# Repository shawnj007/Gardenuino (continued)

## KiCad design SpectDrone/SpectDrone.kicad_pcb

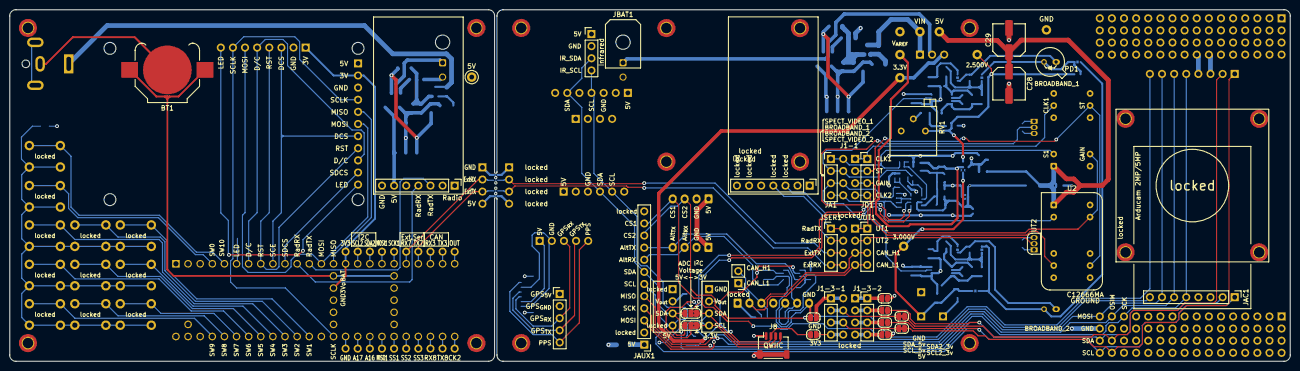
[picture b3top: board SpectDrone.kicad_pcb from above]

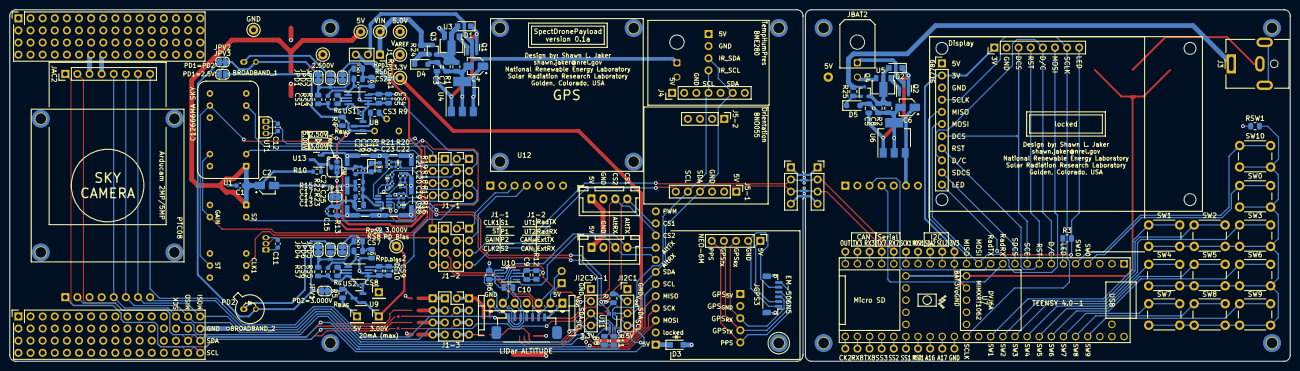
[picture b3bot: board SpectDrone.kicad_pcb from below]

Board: 4 copper layers, 268.4 x 73.7 mm, 233 parts (157 on the bottom side), 135 nets.

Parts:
BT1: Battery_Cell; BatteryHolder_Keystone_3000_1x12mm
C1, C11, C12, C14, C27: 0.1uF; C_0603_1608Metric
C2, C4, C6: 10uF; CP_Elec_3x5.4
C3, C5, C7, C8, C9, C10: 0.1uF; C_0805_2012Metric
C13: 10uF; C_0805_2012Metric
C15: 2.5pF; C_0402_1005Metric
C16: X; CP_EIA-2012-15_AVX-P
C17: X; C_0603_1608Metric
C18, C19, C20, C21, C22, C23, C24, C25: X; C_0402_1005Metric
C26: 1pF; C_0402_1005Metric
C28, C29: C_Polarized; C_Elec_6.3x7.7
CS1, CS6: 11.1pF; C_0603_1608Metric
CS2, CS3, CS7, CS8: 1.11pF; C_0402_1005Metric
CS4, CS9: 10uF; C_0805_2012Metric
CS5, CS10: 0.1uF; C_0805_2012Metric
D1, D2: D; Nexperia_CFP3_SOD-123W
D3: Ge; Nexperia_CFP3_SOD-123W
D4, D5: HPZR-C6V7X; D_SOD-123F
H1, H2, H3, H4, H5, H6, H7, H8, H9, H10, H11, H12, H13, H14, H15, H16: MountingHole; MountingHole_2.2mm_M2_ISO14580_Pad_TopBottom
H17, H18, H19, H20: MountingHole; MountingHole_2.5mm
J1: Conn_01x03_Socket; PinSocket_1x03_P2.54mm_Vertical
J1-1: Conn_02x03_Counter_Clockwise; PinSocket_2x04_P2.54mm_Vertical_renumber
J1-3-1, J1-3-2: Conn_01x04_Male; PinHeader_1x04_P2.54mm_Vertical
J3: Barrel_Jack; BarrelJack_CUI_PJ-063AH_Horizontal
J3V0-1, J5V3-2: Conn_01x01_Male; PinHeader_1x01_P2.54mm_Vertical
J3V2: Conn_01x01_Female; SolderWire-0.1sqmm_1x01_D0.4mm_OD1mm
J4: BME280; PinHeader_1x07_P2.54mm_Vertical
J5: RFShield_OnePiece; Laird_Technologies_BMI-S-101_13.66x12.70mm
J5-1: BNO055-1; PinHeader_1x06_P2.54mm_Vertical
J5-2: BNO055-2; PinHeader_1x04_P2.54mm_Vertical
J6, J7: Conn_02x16_Counter_Clockwise; PinSocket_4x16_P2.54mm_Vertical
J8: QWICK; JST_SH_SM04B-SRSS-TB_1x04-1MP_P1.00mm_Horizontal
JA1: Conn_01x04_Male; PinHeader_1x04_P2.54mm_Vertical
JA10, JA11, JA12, JA13, JA16, JA17: Conn_01x01_Female; SolderWire-0.1sqmm_1x01_D0.4mm_OD1mm
JAC1, JAC2: Conn_01x08_Female; ArduCam2MP
JALT1: ALTITUDE; JST_EH_S7B-EH_1x07_P2.50mm_Horizontal
JALT2: ALTITUDE; PicoBlade_1x07-1MP_P1.25mm_Horizontal
JAPC-1, JAPC-2: APC220; PinHeader_1x07_P2.54mm_Vertical
JAUX1: AUX; PinHeader_1x12_P2.54mm_Vertical
JBAT1, JBAT2: Conn_01x02_Female; Molex_Micro-Fit_3.0_43045-0200_2x01_P3.00mm_Horizontal
JCAM1, JCAM2: Camera; JST_XH_B4B-XH-A_1x04_P2.50mm_Vertical
JCK2: Conn_01x01_Female; SolderWire-0.1sqmm_1x01_D0.4mm_OD1mm
JD1: Conn_01x04_Male; PinHeader_1x04_P2.54mm_Vertical
JDIS1: Display; PinHeader_1x08_P2.54mm_Vertical
JDIS2: Display; PinHeader_1x11_P2.54mm_Vertical
JGND1: Conn_01x01_Female; SolderWire-0.1sqmm_1x01_D0.4mm_OD1mm
JGND1-2: Conn_01x01_Male; PinHeader_1x01_P2.54mm_Vertical
JGPS1, JGPS2: GPS; PinHeader_1x05_P2.54mm_Vertical
JGPS3: GPS; JST_SH_BM06B-SRSS-TB_1x06-1MP_P1.00mm_Vertical
JI2C1, JI2C3v-1: Conn_01x04_Male; PinHeader_1x04_P2.54mm_Vertical
JIF1: Payload; PinHeader_1x04_P2.54mm_Vertical
JIF2: Base; PinSocket_1x04_P2.54mm_Vertical
JIR1: Infrared; PinHeader_1x04_P2.54mm_Vertical
JMISO1: Conn_01x01_Female; SolderWire-0.1sqmm_1x01_D0.4mm_OD1mm
JOUT1: Conn_01x01_Female; SolderWire-0.1sqmm_1x01_D0.4mm_OD1mm
JP3, JP4, JP5, JP6, JP9, JP10: SolderJumper_2_Open; SolderJumper-2_P1.3mm_Open_RoundedPad1.0x1.5mm
JP7: SolderJumper_2_Bridged; SolderJumper-2_P1.3mm_Bridged_RoundedPad1.0x1.5mm
JP8: SolderJumper_2_Open; SolderJumper-2_P1.3mm_Bridged_RoundedPad1.0x1.5mm
JP11: SolderJumper_2_Bridged; SolderJumper-2_P1.3mm_Bridged2Bar_RoundedPad1.0x1.5mm
JP12, JP13, JP14, JP15: SolderJumper_2_Bridged; BreakableJumper
JP16: SolderJumper_3_Bridged12; SolderJumper-4_P1.3mm_Bridged2Bar12_RoundedPad
JP17, JP18: SolderJumper_3_Bridged12; SolderJumper-3_P1.3mm_Bridged2Bar12_RoundedPad1.0x1.5mm
JPD1, JPD3, JPD4, JPD6: SolderJumper_2_Bridged; SolderJumper-2_P1.3mm_Bridged_RoundedPad1.0x1.5mm
JPD2, JPD5: SolderJumper_2_Open; SolderJumper-2_P1.3mm_Open_RoundedPad1.0x1.5mm
JPV1, JPV2: SolderJumper_2_Bridged; SolderJumper-2_P1.3mm_Bridged_RoundedPad1.0x1.5mm
JPV3: SolderJumper_2_Open; SolderJumper-2_P1.3mm_Open_RoundedPad1.0x1.5mm
JRX3, JRX7, JRX8: Conn_01x01_Female; SolderWire-0.1sqmm_1x01_D0.4mm_OD1mm
JSER1: Conn_01x04_Male; PinHeader_1x04_P2.54mm_Vertical
JSS1, JSS2, JSS3: Conn_01x01_Female; SolderWire-0.1sqmm_1x01_D0.4mm_OD1mm
JTX3, JTX7, JTX8: Conn_01x01_Female; SolderWire-0.1sqmm_1x01_D0.4mm_OD1mm
JUT1: Conn_01x04_Male; PinHeader_1x04_P2.54mm_Vertical
PD1, PD2: S1336-18BK; S1336
Q1, Q2: FDN340P; SOT-23
Q3, Q4: NPN 50V 1A NPN_BEC; SOT-323_SC-70
R1, R2: 100K; R_0805_2012Metric
R3: 330; R_0805_2012Metric
R4: 250; R_0805_2012Metric
R5: 91; R_0805_2012Metric
R6, R7, R12: 200K; R_0805_2012Metric
R8, R11: 2K2; R_0805_2012Metric
R9: 470K; R_0805_2012Metric
R10: 20; R_0603_1608Metric
R13: 2K; R_0805_2012Metric
R14: 0; R_0603_1608Metric
R15: X; R_0603_1608Metric
R16, R18, R20, R22: 0; R_0402_1005Metric
R17, R19, R21, R23: X; R_0402_1005Metric
R24, R25: 10K; R_0805_2012Metric
RS2, RS5: R_{G}=X; R_0805_2012Metric
RS3, RS6, RS7, RS8: 330; R_0805_2012Metric
RSW1: 10K; R_0805_2012Metric
RV1: 10K; Potentiometer_Bourns_3296P_Horizontal
R_{PD.bias}1, R_{PD.bias}2: 0; R_0805_2012Metric
R_{PD}1, R_{PD}2: X; R_0805_2012Metric
SW0, SW1, SW2, SW3, SW4, SW5, SW6, SW7, SW8, SW9, SW10: SW_Push; SW_PUSH_6mm_H4.3mm
TP1, TP2, TP3, TP4, TP5, TP5v0-1: TestPoint; TestPoint_Keystone_5000-5004_Miniature
TP_{V}REF1: TestPoint; TestPoint_Keystone_5000-5004_Miniature
TPv1-1, TPv1-2: TestPoint; TestPoint_Keystone_5000-5004_Miniature
U1, U2: C12666MA; Hamamatsu_C12666MA
U3, U5: MCP112-450E/TO; SOT-89-3
U4, U6: LM7805_SOT223; SOT-223-3_TabPin2
U7: Teensy4.1; Teensy4.0-1
U8: ADR5041B; SOT-23
U9: ADR5043BRTZ-REEL7; SOT-23
U10: TXS0102DCUR; SSOP-8_2.95x2.8mm_P0.65mm
U11: PCA9306DC; VSSOP-8_2.3x2mm_P0.5mm
U12: AD7991; SOT-23-8
U13: ADR5045B; SOT-23
US1, US2: AD8221; MSOP-8_3x3mm_P0.65mm
UT1, UT2: TSIC716-TO92; TO-92_Eline
locked: locked; PinSocket_2x04_P2.54mm_Vertical_renumber
locked#2: locked; PinSocket_2x04_P2.54mm_Vertical_renumber
locked#3: locked; PinHeader_1x02_P2.54mm_Vertical

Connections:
2V5: JP16.3 (B), JPV3.2 (B), R4.2, RV1.1, TPv1-1.1, U8.1 (K)
3V0: J3V0-1.1, JP16.1 (A), JPV1.1 (A), R5.2, TPv1-2.1, U9.1 (K), U9.3 (REF)
5V0: CS4.1, CS5.2, CS9.1, CS10.2, JP16.4 (B), R10.1, TP5v0-1.1, U13.1 (K), U13.3 (REF), US1.8 (Vs+), US2.8 (Vs+)
5V3: C1.1, C2.1, C4.1, C11.1, C12.1, C28.1, C29.1, D3.2 (A), J4.1, J5-1.1, J5V3-2.1, J6.55, JAC1.3, JAC2.3, JALT1.1, JALT2.7, JAPC-1.6, JCAM1.1, JCAM2.1, JGPS2.1, JGPS3.2, JI2C1.2, JIF1.4, JIR1.1, JP4.1 (A), JP15.1 (A), R4.1, R5.1, R6.2, R7.2, R10.2, TP1.1, U1.1 (VCC), U2.1 (VCC), U4.3 (VO), UT1.3 (V+), UT2.3 (V+)
/3V1: C9.1, J1.3, J8.2, JI2C3v-1.2, JP6.1 (A), R8.1, R11.1, R12.2, TP5.1, U10.3 (VCCA), U10.6 (OE), U11.1 (VREF1)
/3V2: J3V2.1, JDIS1.1, JDIS2.2, U7.0-16 (TXS_{e}), U7.15 (3V3)
/3v_RX: JALT1.6, JALT2.2, U10.4 (A2)
/3v_TX: JALT1.5, JALT2.3, U10.5 (A1)
/5V4: C6.1, JAPC-2.6, JDIS2.1, JIF2.4, JP15.2 (B), TP4.1, U6.3 (VO), U7.48 (VIN)
/6V1: C3.2, D1.1 (K), Q1.2 (S), U4.1 (VI)
/6V2: C5.2, D2.1 (K), Q2.2 (S), U6.1 (VI)
/A16: JA16.1, U7.32 (40_A16)
/A17: JA17.1, U7.33 (41_A17)
/ALT_RX: JAUX1.8, JCAM2.3, U10.1 (B2)
/ALT_TX: JAUX1.9, JCAM2.4, U10.8 (B1)
/APC2RX: JAPC-2.4, U7.11 (9_OUT1C)
/APC2TX: JAPC-2.3, U7.12 (10_CS_MQSR)
/APCRX: JAPC-1.4, JSER1.2, locked.7
/APCTX: JAPC-1.3, JSER1.1, locked.8
/BKL: JDIS1.8, JDIS2.11, R3.2
/Broadband Photodiodes/INV1: JPD3.2 (B), RS6.1, R_{PD.bias}1.1, R_{PD}1.2
/Broadband Photodiodes/INV2: JPD6.2 (B), RS8.1, R_{PD.bias}2.1, R_{PD}2.2
/CAN_H: JALT1.3, JALT2.5, JUT1.3, locked.3, locked#3.2
/CAN_L: JALT1.2, JALT2.6, JUT1.4, locked.4, locked#3.1
/CK2: JCK2.1, U7.25 (33_MCLK2)
/CLK1: J1-1.1, JD1.1, U1.4 (CLK)
/CLK2: J1-1.4, JD1.4, U2.4 (CLK)
/CS1: JAC1.8, JAUX1.11, JCAM1.4
/CS2: JAC2.8, JAUX1.10, JCAM1.3
/DCS: JDIS1.3, JDIS2.7, U7.9 (7_RX2_OUT1A)
/D/C: JDIS1.5, JDIS2.9, U7.7 (5_IN2)
/GAIN: J1-1.3, JD1.3, U1.9 (GAIN), U2.9 (GAIN)
/GPSRX: JGPS1.3, JGPS2.3, JGPS3.3
/GPSTX: JGPS1.4, JGPS2.4, JGPS3.4
/LED: R3.1, U7.6 (4_BCLK2)
/MISO1: JMISO1.1, U7.31 (39_MISO1_OUT1A)
/MISO_T: JDIS2.5, U7.14 (12_MISO_MQSL)
/MOSI1: JA12.1, U7.18 (26_A12_MOSI1)
/MOSI_T: JDIS1.6, JDIS2.6, U7.13 (11_MOSI_CTX1)
/OUT: JOUT1.1, U7.24 (32_OUT1B)
/PPS: JGPS1.5, JGPS2.5, JGPS3.6
/RST: JDIS1.4, JDIS2.8, U7.8 (6_OUT1D)
/RX: JIF1.3, JP14.1 (A), JSER1.4, locked.5
/RX3: JRX3.1, U7.22 (30_CRX3)
/RX7: JIF2.2, JP13.2 (B), JRX7.1, U7.20 (28_RX7)
/RX8: JRX8.1, U7.26 (34_RX8)
/SCK1: JA13.1, U7.19 (27_A13_SCK1)
/SCL2: JA10.1, U7.16 (24_A10_TX6_SCL2)
/SCL3: J8.4, JI2C3v-1.4, JP17.1 (A), R8.2, U11.2 (SCL1)
/SCLK: JDIS1.7, JDIS2.4, U7.35 (13_SCK_LED)
/SCL_{RF}: JP17.2 (C), U12.1 (SCL)
/SDA2: JA11.1, U7.17 (25_A11_RX6_SDA2)
/SDA3: J8.3, JI2C3v-1.3, JP18.1 (A), R11.2, U11.3 (SDA1)
/SDA_{RF}: JP18.2 (C), U12.2 (SDA)
/SDCS: JDIS2.10, U7.10 (8_TX2_IN1)
/SS1: JSS1.1, U7.30 (38_CS1_IN1)
/SS2: JSS2.1, U7.29 (37_CS)
/SS3: JSS3.1, U7.28 (36_CS)
/ST: J1-1.2, JD1.2, U1.7 (ST), U2.7 (ST)
/SW0: SW0.1, U7.4 (2_OUT2)
/SW1: SW1.1, U7.37 (15_A1_RX3_SPDIF_IN)
/SW2: SW2.1, U7.38 (16_A2_RX4_SCL1)
/SW3: SW3.1, U7.39 (17_A3_TX4_SDA1)
/SW4: SW4.1, U7.40 (18_A4_SDA)
/SW5: SW5.1, U7.41 (19_A5_SCL)
/SW6: SW6.1, U7.42 (20_A6_TX5_LRCLK1)
/SW7: SW7.1, U7.43 (21_A7_RX5_BCLK1)
/SW8: SW8.1, U7.44 (22_A8_CTX1)
/SW9: SW9.1, U7.45 (23_A9_CRX1_MCLK1)
/SW10: SW10.1, U7.5 (3_LRCLK2)
/TX: JIF1.2, JP13.1 (A), JSER1.3, locked.6
/TX3: JTX3.1, U7.23 (31_CTX3)
/TX7: JIF2.3, JP14.2 (B), JTX7.1, U7.21 (29_TX7)
/TX8: JTX8.1, U7.27 (35_TX8)
/UT1: JUT1.1, UT1.2 (Signal), locked.1
/UT2: JUT1.2, UT2.2 (Signal), locked.2
/VBAT1: J1.2, JBAT1.1, Q1.3 (D)
/VBAT2: JBAT2.1, Q2.3 (D)
/VBAT_RTC: BT1.1 (+), U7.0-15 (VBAT), U7.50 (VBAT)
/VDC1: C7.2, D1.2 (A), Q3.2 (E), R1.2, U3.2 (VDD)
/VDC2: C8.2, D2.2 (A), Q4.2 (E), R2.2, U5.2 (VDD)
/VIN1: J1.1, Q3.3 (C), R24.2, TP2.1
/VIN2: J3.1, Q4.3 (C), R25.2
GND1: C1.2, C2.2, C3.1, C4.2, C7.1, C9.2, C10.2, C11.2, C12.2, C13.2, C14.2, C15.2, C28.2, C29.2, CS2.2, CS3.2, CS4.2, CS5.1, CS7.2, CS8.2, CS9.2, CS10.1, D4.2 (A), J4.3, J5-1.3, J6.56, J7.32, J8.1, J8.MP, JAC1.4, JAC2.4, JALT1.7, JALT2.1, JAPC-1.7, JAUX1.2, JBAT1.2, JCAM1.2, JCAM2.2, JGND1-2.1, JGPS2.2, JGPS3.1, JGPS3.5, JGPS3.MP, JI2C1.1, JI2C3v-1.1, JIF1.1, JIR1.2, JP3.1 (A), JP5.1 (A), JP11.1 (A), JP12.1 (A), R1.1, R12.1, R13.2, RV1.3, R_{PD.bias}1.2, R_{PD.bias}2.2, TP3.1, U1.3 (GND), U1.5 (CASE), U2.3 (GND), U2.5 (CASE), U3.3 (VSS), U4.2 (GND), U8.2 (A), U9.2 (A), U10.2 (GND), U11.4 (GND), U12.7 (GND), US1.5 (Vs-), US1.6 (Ref), US2.5 (Vs-), US2.6 (Ref), UT1.1 (GND), UT2.1 (GND)
GND2: BT1.2 (-), C5.1, C6.2, C8.1, D5.2 (A), J3.2, JAPC-2.7, JBAT2.2, JDIS1.2, JDIS2.3, JGND1.1, JIF2.1, JP12.2 (B), R2.1, RSW1.1, U5.3 (VSS), U6.2 (GND), U7.0-17 (GND), U7.1 (GND), U7.34 (GND), U7.47 (GND), U7.52 (GND)
GND_{RF}: C15.1, C17.2, C19.2, C21.2, C23.2, C25.2, J5.1 (Shield), JP11.2 (B), R13.1, R15.1, R17.1, R19.1, R21.1, R23.1, U13.2 (A)
MISO: J7.15, JAC1.6, JAC2.6, JAUX1.5
MOSI: J7.16, JAC1.7, JAC2.7, JAUX1.3
unnamed: D3.1 (K), JAUX1.1
unnamed: D4.1 (K), Q3.1 (B), R24.1
unnamed: D5.1 (K), Q4.1 (B), R25.1
unnamed: J1-3-1.1, JP5.2 (B), locked#2.8
unnamed: J1-3-1.2, JP7.2 (B), locked#2.7
unnamed: J1-3-1.3, JP8.2 (B), locked#2.6
unnamed: J1-3-1.4, JP6.2 (B), locked#2.5
unnamed: J1-3-2.1, JP3.2 (B), locked#2.1
unnamed: J1-3-2.2, JP9.2 (B), locked#2.2
unnamed: J1-3-2.3, JP10.2 (B), locked#2.3
unnamed: J1-3-2.4, JP4.2 (B), locked#2.4
unnamed: JPD1.2 (B), JPD2.2 (B), RS3.1, R_{PD}1.1
unnamed: JPD2.1 (A), JPD3.1 (A), PD1.1 (A)
unnamed: JPD4.2 (B), JPD5.2 (B), RS7.1, R_{PD}2.1
unnamed: JPD5.1 (A), JPD6.1 (A), PD2.1 (A)
unnamed: Q1.1 (G), U3.1 (OUT)
unnamed: Q2.1 (G), U5.1 (OUT)
unnamed: R9.2, RV1.2
unnamed: RS2.1, US1.3 (Rg)
unnamed: RS2.2, US1.2 (Rg)
unnamed: RS5.1, US2.3 (Rg)
unnamed: RS5.2, US2.2 (Rg)
unnamed: RSW1.2, SW0.2, SW1.2, SW2.2, SW3.2, SW4.2, SW5.2, SW6.2, SW7.2, SW8.2, SW9.2, SW10.2
unnamed: R9.1, U8.3 (REF)
unnamed: C10.1, R6.1, U10.7 (VCCB)
unnamed: R7.1, U11.7 (VREF2), U11.8 (EN)
unnamed: CS1.1, CS3.1, RS3.2, US1.4 (+)
unnamed: CS1.2, CS2.1, RS6.2, US1.1 (-)
unnamed: CS6.1, CS8.1, RS7.2, US2.4 (+)
unnamed: CS6.2, CS7.1, RS8.2, US2.1 (-)
P1: C24.1, J1-1.7, JA1.2, R22.2, US1.7
P1_{RF}: C24.2, C25.1, R22.1, R23.2, U12.5 (Vin2)
P2: C20.1, J1-1.6, JA1.3, R18.2, US2.7
P2_{RF}: C20.2, C21.1, R18.1, R19.2, U12.4 (Vin1)
PD1: JPD1.1 (A), JPV2.2 (B), JPV3.1 (A), PD1.2 (K)
PD2: JPD4.1 (A), JPV1.2 (B), JPV2.1 (A), PD2.2 (K)
S1: C22.1, J1-1.8, JA1.1, R20.2, U1.2 (VIDEO)
S1_{RF}: C22.2, C23.1, R20.1, R21.2, U12.6 (Vin3)
S2: C18.1, J1-1.5, JA1.4, R16.2, U2.2 (VIDEO)
S2_{RF}: C18.2, C19.1, R16.1, R17.2, U12.3 (Vin0)
SCK: J7.14, JAC1.5, JAC2.5, JAUX1.4
SCL: J4.4, J5-1.5, J7.64, JAC1.1, JAUX1.6, JI2C1.4, JIR1.4, JP10.1 (A), JP17.3 (B), U11.6 (SCL2)
SCL4: J7.63, JAC2.1, JP8.1 (A)
SDA: J4.6, J5-1.4, J7.48, JAC1.2, JAUX1.7, JI2C1.3, JIR1.3, JP9.1 (A), JP18.3 (B), U11.5 (SDA2)
SDA4: J7.47, JAC2.2, JP7.1 (A)
V_{AREF}: C16.1, C26.1, C27.1, JP16.2 (C), R14.1, TP_{V}REF1.1
V_{RF}: C13.1, C14.1, C16.2, C17.1, C26.2, C27.2, R14.2, R15.2, U12.8 (VDD)

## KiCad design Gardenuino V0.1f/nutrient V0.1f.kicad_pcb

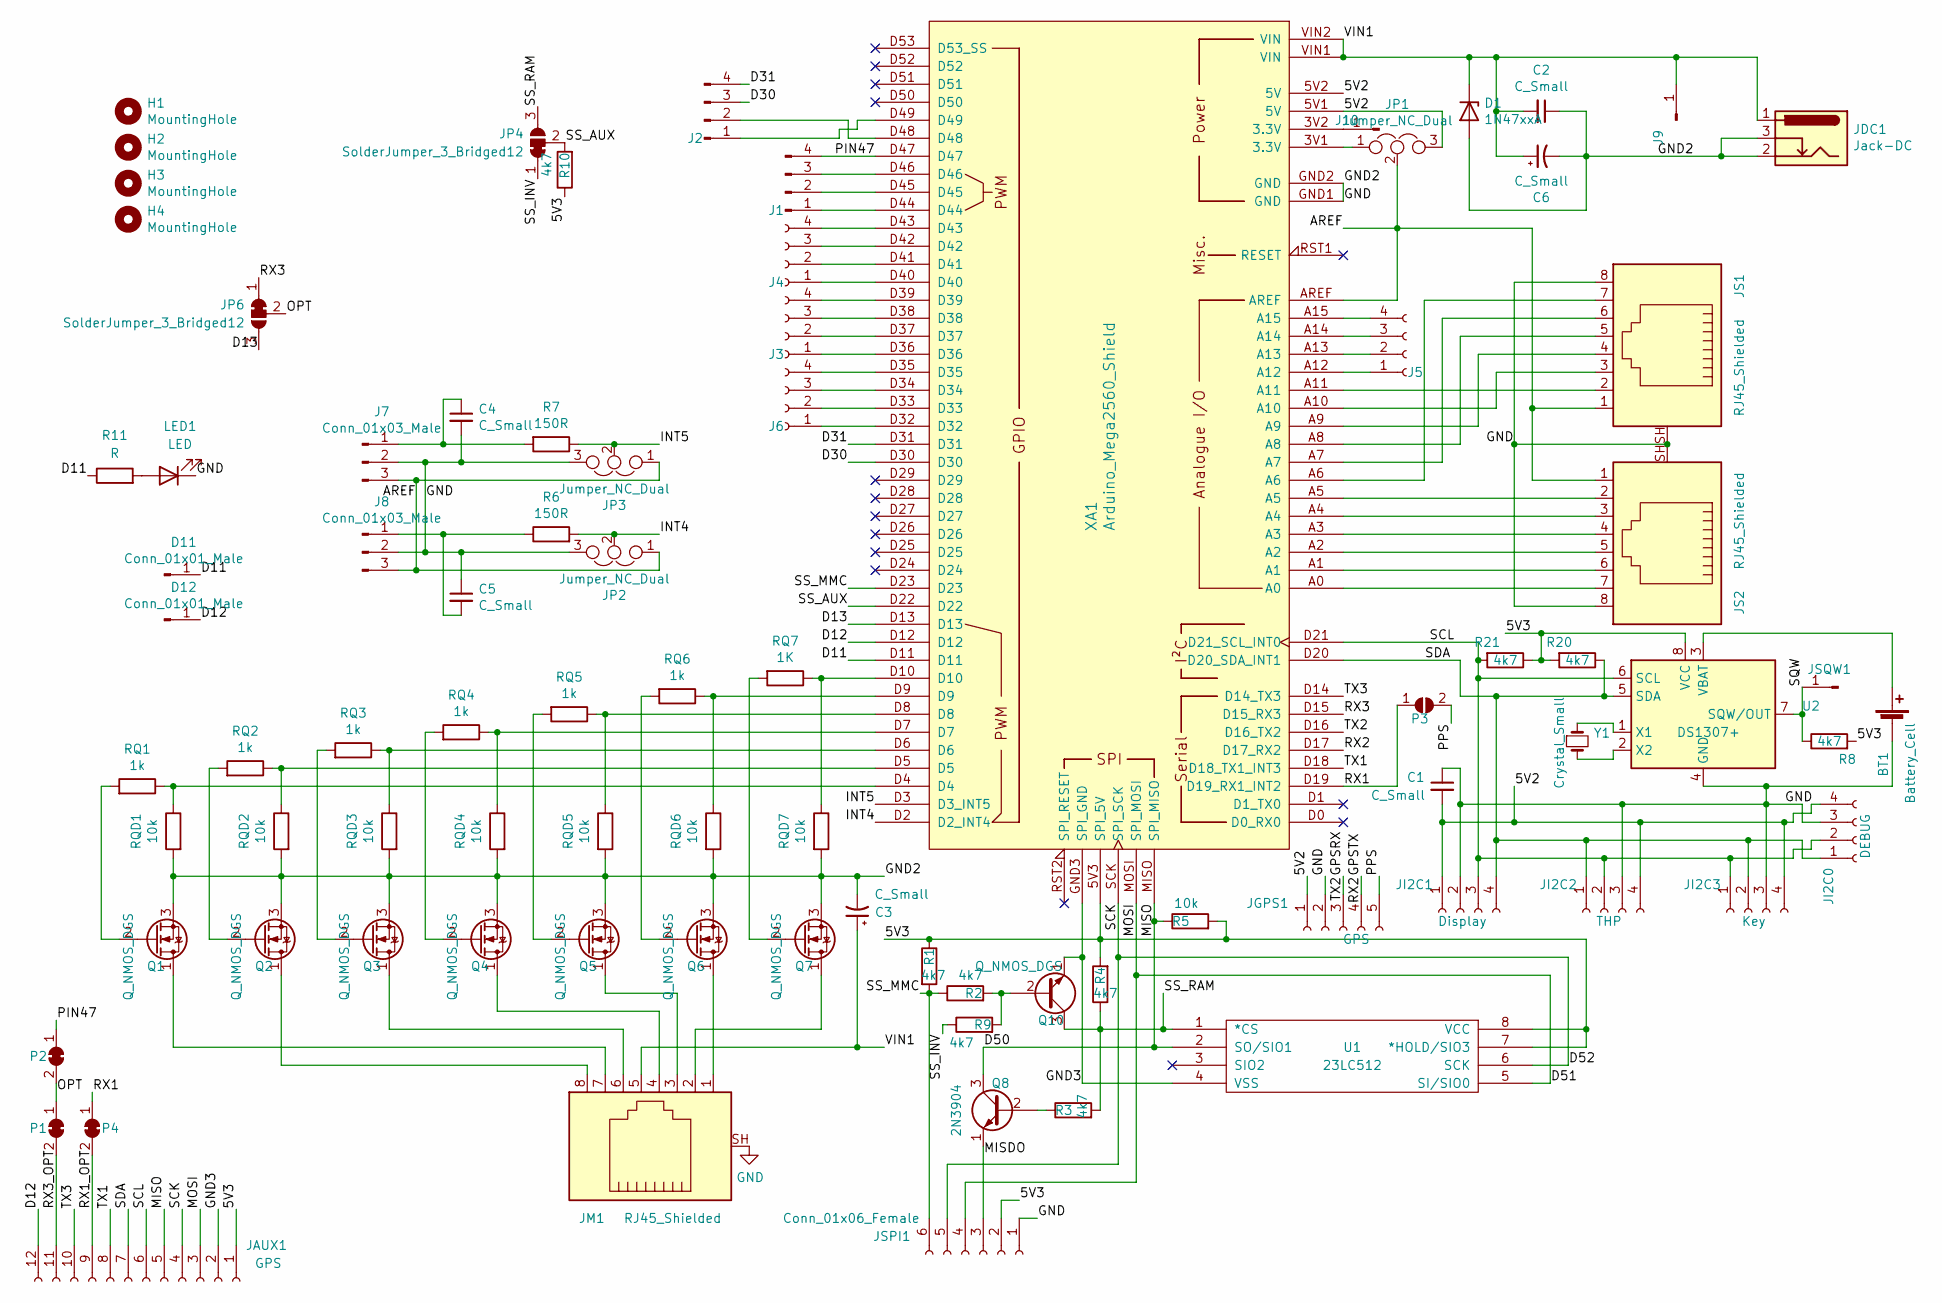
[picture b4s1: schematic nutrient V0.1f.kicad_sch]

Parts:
BT1: Battery_Cell; BatteryHolder_Keystone_2998_1x6.8mm
C1, C2: C_Small; C_Disc_D3.0mm_W1.6mm_P2.50mm
C3, C6: C_Small; CP_Radial_D4.0mm_P2.00mm
C4, C5: C_Small; C_Disc_D4.3mm_W1.9mm_P5.00mm
D1: 1N47xxA; D_DO-41_SOD81_P5.08mm_Vertical_AnodeUp
D11, D12: Conn_01x01_Male; PinHeader_1x01_P2.54mm_Vertical
H1, H2, H3, H4: MountingHole; MountingHole_2.2mm_M2_ISO14580_Pad_TopBottom
J1, J2: Conn_01x04_Male; PinHeader_1x04_P2.54mm_Vertical
J3, J5, J6: Conn_01x04_Female; PinSocket_1x04_P2.54mm_Vertical
J4: Conn_01x04_Male; PinSocket_1x04_P2.54mm_Vertical
J7, J8: Conn_01x03_Male; JST_EH_S3B-EH_1x03_P2.50mm_Horizontal
J9, J10: Conn_01x01_Male; PinHeader_1x01_P2.54mm_Vertical
JAUX1: GPS; PinSocket_1x12_P2.54mm_Vertical
JDC1: Jack-DC; BarrelJack_Horizontal
JGPS1: GPS; PinSocket_1x05_P2.54mm_Vertical
JI2C0: DEBUG; PinSocket_1x04_P2.54mm_Vertical
JI2C1: Display; PinSocket_1x04_P2.54mm_Vertical
JI2C2: THP; PinSocket_1x04_P2.54mm_Vertical
JI2C3: Key; PinHeader_1x04_P2.54mm_Horizontal
JM1: RJ45_Shielded; RJ45_Ninigi_GE1
JP1, JP2, JP3: Jumper_NC_Dual; PinHeader_1x03_P2.54mm_Vertical
JP4, JP6: SolderJumper_3_Bridged12; SolderJumper-3_P1.3mm_Bridged2Bar12_RoundedPad1.0x1.5mm_nar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
JS1, JS2: RJ45_Shielded; RJ45_Ninigi_GE1
JSPI1: Conn_01x06_Female; PinSocket_1x06_P2.54mm_Horizontal_SDREADER_KEEPOUT
JSQW1: Conn_01x01_Male; PinHeader_1x01_P2.54mm_Vertical
LED1: LED; LED_D3.0mm
P1, P2, P4: SolderJumper_2_Bridged; SolderJumper-2_P1.3mm_Bridged2Bar_RoundedPad1.0x1.5mm
P3: SolderJumper_2_Bridged; SolderJumper-2_P1.3mm_Bridged2Bar_RoundedPad1.0x1.5mm_narrow
Q1, Q2, Q3, Q4, Q5, Q6, Q7: Q_NMOS_DGS; TO-92L_Inline_Wide_Flat
Q8: 2N3904; TO-92L_Inline_Wide
Q10: Q_NMOS_DGS; TO-92L_Inline_Wide
R1, R4, R8, R20, R21: 4k7; R_Axial_DIN0204_L3.6mm_D1.6mm_P5.08mm_Horizontal
R2, R3, R9: 4k7; R_Axial_DIN0204_L3.6mm_D1.6mm_P2.54mm_Vertical
R5: 10k; R_Axial_DIN0204_L3.6mm_D1.6mm_P5.08mm_Horizontal
R6, R7: 150R; R_Axial_DIN0207_L6.3mm_D2.5mm_P2.54mm_Vertical
R10: 4k7
R11: R; R_Axial_DIN0204_L3.6mm_D1.6mm_P5.08mm_Horizontal
RQ1, RQ2, RQ3, RQ4, RQ5, RQ6: 1k; R_Axial_DIN0207_L6.3mm_D2.5mm_P7.62mm_Horizontal
RQ7: 1K; R_Axial_DIN0207_L6.3mm_D2.5mm_P7.62mm_Horizontal
RQD1, RQD2, RQD3, RQD4, RQD5, RQD6, RQD7: 10k; R_Axial_DIN0204_L3.6mm_D1.6mm_P5.08mm_Horizontal
U1: 23LC512; DIP-8_W7.62mm
U2: DS1307+; DIP-8_W7.62mm
XA1: Arduino_Mega2560_Shield; Arduino_2560_Mega_Embad
Y1: Crystal_Small; Crystal_DS10_D1.0mm_L4.3mm_Vertical

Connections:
/5V2: C1.2, JGPS1.1, JI2C0.4, JI2C1.1, JI2C2.4, JI2C3.4, JP1.3, XA1.5V1 (5V), XA1.5V2 (5V)
/5V3: JAUX1.1, JSPI1.2, R1.1, R4.2, R5.2, R8.2, R10.1, R20.2, R21.1, U1.7 (*HOLD/SIO3), U1.8 (VCC), U2.8 (VCC), XA1.5V3 (SPI_5V)
/AREF: J7.3, J8.3, JP1.2, JP2.1, JP3.1, JS1.1, JS2.1, XA1.AREF
/D11: D11.1, R11.1, XA1.D11
/D12: D12.1, JAUX1.12, XA1.D12
/D13: JP6.3 (B), XA1.D13
/D30: J2.3, XA1.D30
/D31: J2.4, XA1.D31
/D50: JAUX1.5, Q8.3 (C), R5.1, U1.2 (SO/SIO1), XA1.MISO (SPI_MISO)
/D51: JAUX1.3, JSPI1.4, U1.5 (SI/SIO0), XA1.MOSI (SPI_MOSI)
/D52: JAUX1.4, JSPI1.5, U1.6 (SCK), XA1.SCK (SPI_SCK)
/GND3: JAUX1.2, Q10.1 (E), U1.4 (VSS), XA1.GND3 (SPI_GND)
/GPSRX: JGPS1.3, XA1.D16 (D16_TX2)
/GPSTX: JGPS1.4, XA1.D17 (D17_RX2)
/INT4: JP2.2, R6.2, XA1.D2 (D2_INT4)
/INT5: JP3.2, R7.1, XA1.D3 (D3_INT5)
/MISDO: JSPI1.3, Q8.1 (E)
/OPT: JP6.2 (C), P1.1 (A), P2.2 (B)
/PIN47: J1.4, P2.1 (A), XA1.D47
/PPS: JGPS1.5, P3.2 (B)
/RX1: P3.1 (A), P4.1 (A), XA1.D19 (D19_RX1_INT2)
/RX1_OPT: JAUX1.9, P4.2 (B)
/RX3: JP6.1 (A), XA1.D15 (D15_RX3)
/RX3_OPT: JAUX1.11, P1.2 (B)
/SCL: JAUX1.6, JI2C0.2, JI2C1.3, JI2C2.2, JI2C3.1, R21.2, U2.6 (SCL), XA1.D21 (D21_SCL_INT0)
/SDA: JAUX1.7, JI2C0.1, JI2C1.4, JI2C2.1, JI2C3.2, R20.1, U2.5 (SDA), XA1.D20 (D20_SDA_INT1)
/SQW: JSQW1.1, R8.1, U2.7 (SQW/OUT)
/SS_AUX: JP4.2 (C), R10.2, XA1.D22
/SS_INV: JP4.1 (A), R9.1
/SS_MMC: JSPI1.6, R1.2, R2.1, XA1.D23
/SS_RAM: JP4.3 (B), Q10.3 (C), R3.2, R4.1, U1.1 (*CS)
/TX1: JAUX1.8, XA1.D18 (D18_TX1_INT3)
/TX3: JAUX1.10, XA1.D14 (D14_TX3)
/VIN1: C2.2, C3.1, C6.1, D1.1 (K), J9.1, JDC1.1, JM1.5, XA1.VIN1 (VIN), XA1.VIN2 (VIN)
GND: BT1.2 (-), C1.1, C2.1, C3.2, C4.2, C5.1, C6.2, D1.2 (A), J7.2, J8.2, JDC1.2, JDC1.3, JGPS1.2, JI2C0.3, JI2C1.2, JI2C2.3, JI2C3.3, JM1.SH, JP2.3, JP3.3, JS1.8, JS1.SH, JS2.8, JS2.SH, JSPI1.1, LED1.1 (K), Q1.3 (S), Q2.3 (S), Q3.3 (S), Q4.3 (S), Q5.3 (S), Q6.3 (S), Q7.3 (S), RQD1.2, RQD2.2, RQD3.2, RQD4.2, RQD5.2, RQD6.2, RQD7.2, U2.4 (GND), XA1.GND1 (GND), XA1.GND2 (GND)
unnamed: BT1.1 (+), U2.3 (VBAT)
unnamed: C4.1, J7.1, R7.2
unnamed: C5.2, J8.1, R6.1
unnamed: J1.1, XA1.D44
unnamed: J1.2, XA1.D45
unnamed: J1.3, XA1.D46
unnamed: J2.1, XA1.D49
unnamed: J2.2, XA1.D48
unnamed: J3.1, XA1.D36
unnamed: J3.2, XA1.D37
unnamed: J3.3, XA1.D38
unnamed: J3.4, XA1.D39
unnamed: J4.1, XA1.D40
unnamed: J4.2, XA1.D41
unnamed: J4.3, XA1.D42
unnamed: J4.4, XA1.D43
unnamed: J5.1, XA1.A12
unnamed: J5.2, XA1.A13
unnamed: J5.3, XA1.A14
unnamed: J5.4, XA1.A15
unnamed: J6.1, XA1.D32
unnamed: J6.2, XA1.D33
unnamed: J6.3, XA1.D34
unnamed: J6.4, XA1.D35
unnamed: J10.1, XA1.3V2 (3.3V)
unnamed: JM1.1, Q6.1 (D)
unnamed: JM1.2, Q7.1 (D)
unnamed: JM1.3, Q5.1 (D)
unnamed: JM1.4, Q4.1 (D)
unnamed: JM1.6, Q3.1 (D)
unnamed: JM1.7, Q1.1 (D)
unnamed: JM1.8, Q2.1 (D)
unnamed: JP1.1, XA1.3V1 (3.3V)
unnamed: JS1.2, XA1.A11
unnamed: JS1.3, XA1.A10
unnamed: JS1.4, XA1.A9
unnamed: JS1.5, XA1.A8
unnamed: JS1.6, XA1.A7
unnamed: JS1.7, XA1.A6
unnamed: JS2.2, XA1.A5
unnamed: JS2.3, XA1.A4
unnamed: JS2.4, XA1.A3
unnamed: JS2.5, XA1.A2
unnamed: JS2.6, XA1.A1
unnamed: JS2.7, XA1.A0
unnamed: LED1.2 (A), R11.2
unnamed: Q1.2 (G), RQ1.2
unnamed: Q2.2 (G), RQ2.2
unnamed: Q3.2 (G), RQ3.2
unnamed: Q4.2 (G), RQ4.2
unnamed: Q5.2 (G), RQ5.2
unnamed: Q6.2 (G), RQ6.2
unnamed: Q7.2 (G), RQ7.2
unnamed: Q8.2 (B), R3.1
unnamed: Q10.2 (B), R2.2, R9.2
unnamed: RQ1.1, RQD1.1, XA1.D4
unnamed: RQ2.1, RQD2.1, XA1.D5
unnamed: RQ3.1, RQD3.1, XA1.D6
unnamed: RQ4.1, RQD4.1, XA1.D7
unnamed: RQ5.1, RQD5.1, XA1.D8
unnamed: RQ6.1, RQD6.1, XA1.D9
unnamed: RQ7.1, RQD7.1, XA1.D10
unnamed: U2.1 (X1), Y1.1
unnamed: U2.2 (X2), Y1.2

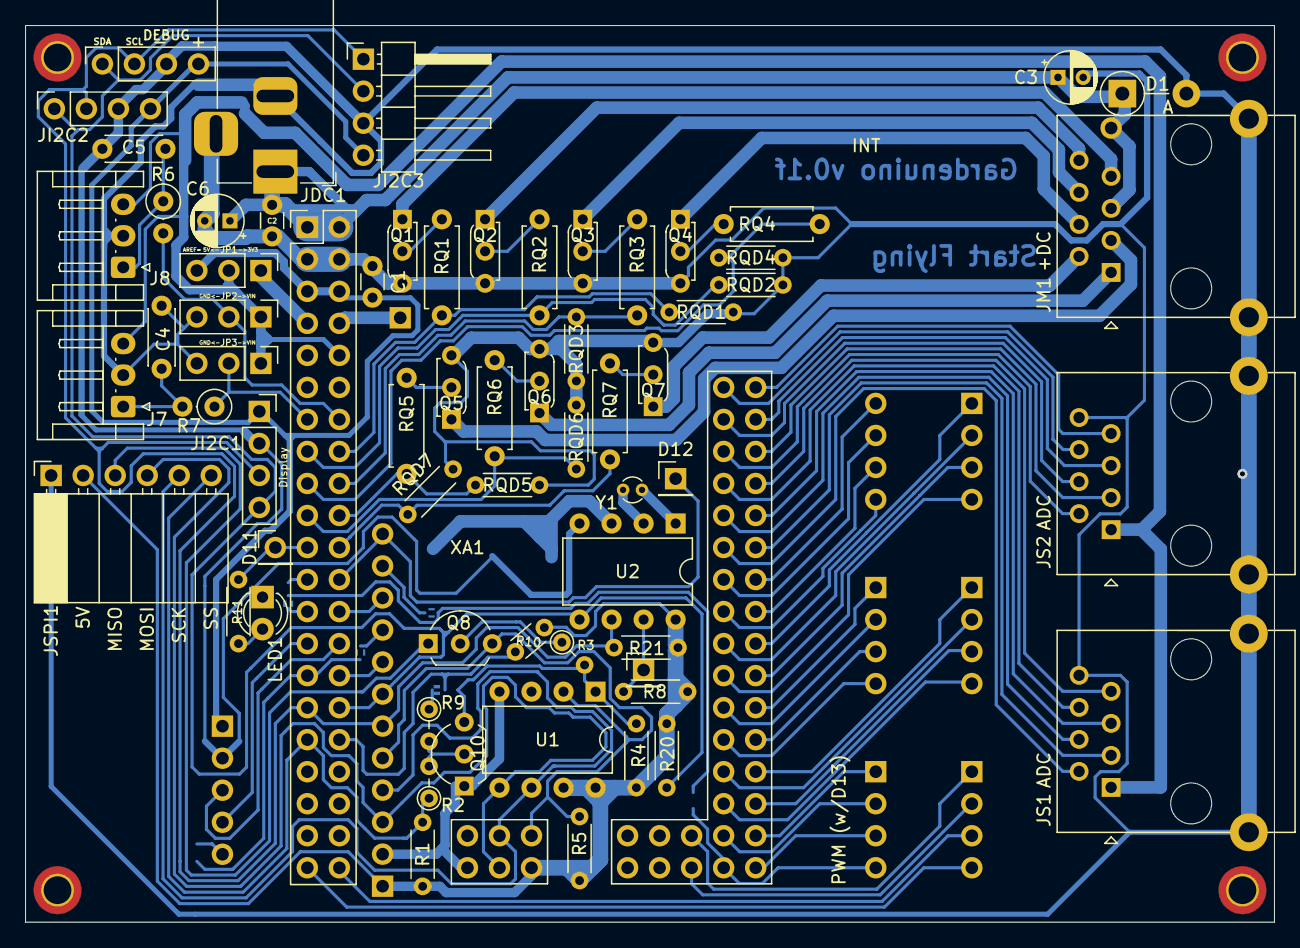
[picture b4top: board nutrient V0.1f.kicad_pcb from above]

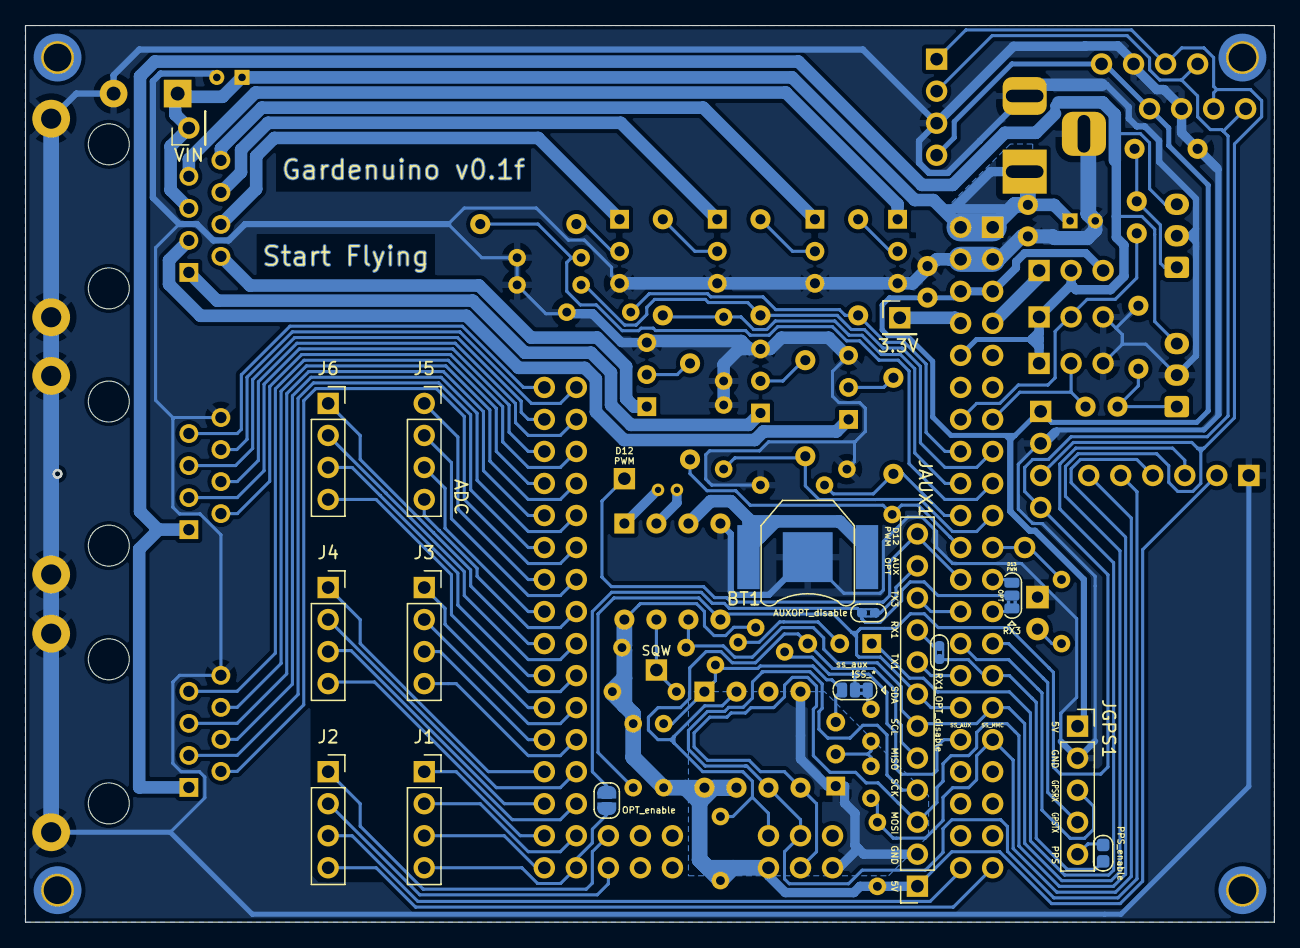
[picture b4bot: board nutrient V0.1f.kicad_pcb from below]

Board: 2 copper layers, 99.1 x 71.1 mm, 86 parts (17 on the bottom side), 99 nets.

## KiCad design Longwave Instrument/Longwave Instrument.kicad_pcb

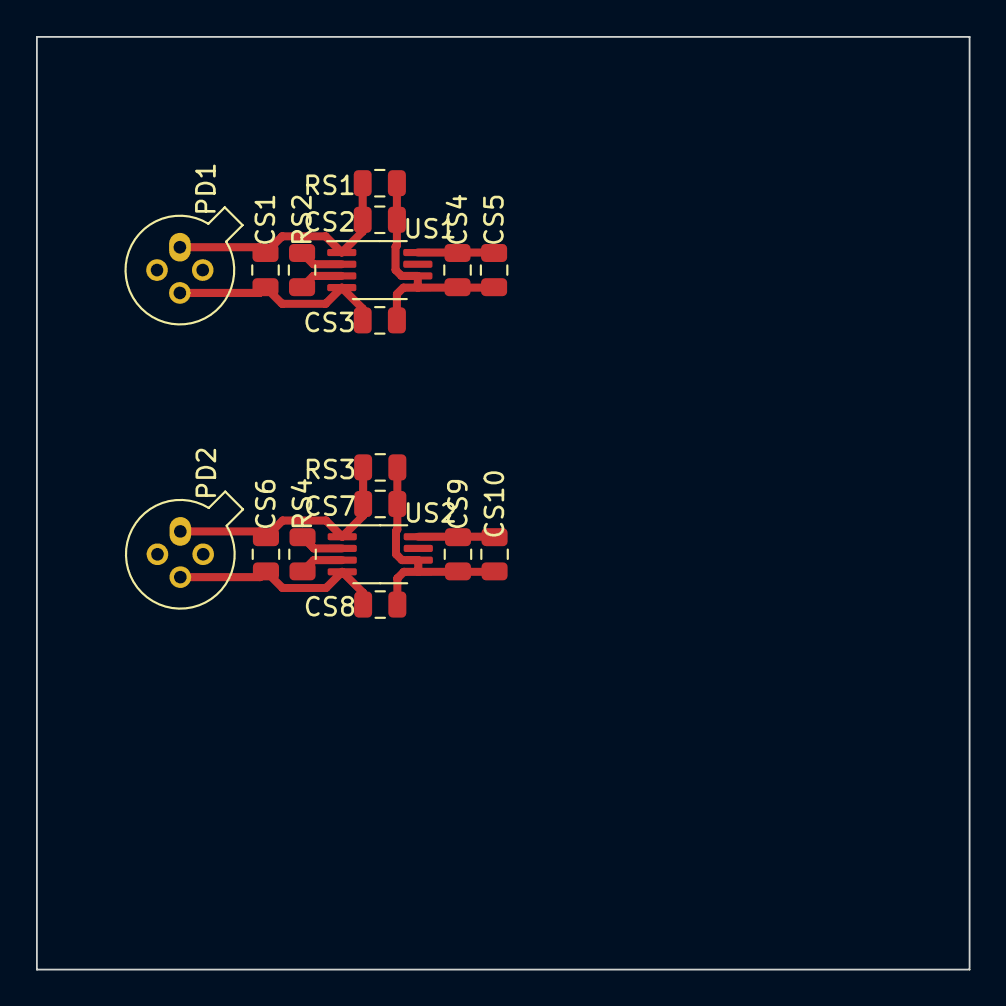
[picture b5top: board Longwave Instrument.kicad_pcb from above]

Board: 2 copper layers, 51.8 x 51.8 mm, 18 parts (0 on the bottom side), 10 nets.

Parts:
CS1, CS6: 10nF; C_0805_2012Metric
CS2, CS3, CS7, CS8: 1nF; C_0805_2012Metric
CS4, CS9: 10uF; C_0805_2012Metric
CS5, CS10: 0.1uF; C_0805_2012Metric
PD1, PD2: S1336-18BK; TO-18-4_Lens
RS1, RS3: 1K0; C_0805_2012Metric
RS2, RS4: 12K4; C_0805_2012Metric
US1, US2: AD8221; MSOP-8_3x3mm_P0.65mm

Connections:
/1.0V: CS1.1, CS3.1, CS6.1, CS8.1, PD1.3 (K), PD2.3 (K), US1.4 (+), US2.4 (+)
/5V3: CS4.1, CS5.2, CS9.1, CS10.2, US1.8 (Vs+), US2.8 (Vs+)
/GND1: CS2.2, CS3.2, CS4.2, CS5.1, CS7.2, CS8.2, CS9.2, CS10.1, RS1.2, RS3.2, US1.5 (Vs-), US1.6 (Ref), US2.5 (Vs-), US2.6 (Ref)
/S2: US1.7, US2.7
/SIG1: CS1.2, CS2.1, PD1.1 (A), RS1.1, US1.1 (-)
/SIG2: CS6.2, CS7.1, PD2.1 (A), RS3.1, US2.1 (-)
unnamed: RS2.1, US1.3 (Rg)
unnamed: RS2.2, US1.2 (Rg)
unnamed: RS4.2, US2.2 (Rg)
unnamed: RS4.1, US2.3 (Rg)

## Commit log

2022-05-01 Minor track changes
2022-05-01 Minor layout change
2022-08-22 External header changes
2022-09-08 Trace changes, GND loop fixes
2023-02-14 New version
2023-02-15 New schematics for specto
2023-02-16 SpectDrone Development
2023-03-01 Add clang-format file for ArduinoIDE
